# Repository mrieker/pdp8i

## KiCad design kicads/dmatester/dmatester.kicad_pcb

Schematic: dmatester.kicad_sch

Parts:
J1, J2, J3, J4: Conn_02x20_Odd_Even; PinHeader_2x20_P2.54mm_Vertical
J5, J6: Conn_01x24; PinHeader_1x24_P2.54mm_Vertical
U2, U118: 74AC20; DIP-14_W7.62mm
U3: 74HC27; DIP-14_W7.62mm
U4, U5, U10, U12, U13, U18, U19, U24: 74AHC540; DIP-20_W7.62mm
U14: 74AHC02; DIP-14_W7.62mm
U15, U16, U17, U26, U27, U28, U29, U33, U34, U35, U36, U37, U39, U40, U42, U43, U44: 74AHC174; DIP-16_W7.62mm
U20, U124, U125, U141: 74AHC04; DIP-14_W7.62mm
U22, U38, U116, U157, U163: 74HC30; DIP-14_W7.62mm
U41, U169: 74AHC74; DIP-14_W7.62mm
U45: 74AHC86; DIP-14_W7.62mm
U54: 74AHC08; DIP-14_W7.62mm
U147, U158, U161: 74AHC00; DIP-14_W7.62mm
U149: 74AC10; DIP-14_W7.62mm
U155: 74HC21; DIP-14_W7.62mm
U167: 74AC11; DIP-14_W7.62mm
U174: 74AC109; DIP-16_W7.62mm
U180: 74AHC541; DIP-20_W7.62mm

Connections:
/CLOK2: J4.3, U10.7 (A5)
/_ACCLEAR: J3.27
/_ACUM_0: J3.4
/_ACUM_1: J2.33
/_ACUM_2: J2.26
/_ACUM_3: J2.19
/_ACUM_4: J2.12
/_ACUM_5: J2.6
/_ACUM_6: J1.36
/_ACUM_7: J1.30
/_ACUM_8: J1.24
/_ACUM_9: J1.17
/_ACUM_10: J1.10
/_ACUM_11: J1.3
/_BRKCYC: J4.32, U12.7 (A5)
/_BRKGNTI: J4.30, U180.8 (A6)
/_BRKGNTO: J4.29, U180.11 (Y7)
/_BRKRQST: J3.28, U12.12 (Y6), U180.7 (A5)
/_BRKWRM: J4.9, U4.13 (Y5)
/_BUSINI: J3.30, U10.6 (A4)
/_BWCOV: J3.31, U12.9 (A7)
/_CAINC: J4.10, U4.14 (Y4)
/_CYCLE3: J4.11, U4.15 (Y3)
/_DFLD_0: J3.19
/_DFLD_1: J3.15
/_DFLD_2: J3.11
/_DMAFLD_0: J3.20, U4.16 (Y2)
/_DMAFLD_1: J3.16, U4.17 (Y1)
/_DMAFLD_2: J3.12, U4.18 (Y0)
/_FIELD_0: J3.22
/_FIELD_1: J3.18
/_FIELD_2: J3.14
/_IFLD_0: J3.21
/_IFLD_1: J3.17
/_IFLD_2: J3.13
/_INBUS_0: J3.7, U13.18 (Y0), U18.18 (Y0)
/_INBUS_1: J2.36, U13.17 (Y1), U18.17 (Y1)
/_INBUS_2: J2.29, U13.16 (Y2), U18.16 (Y2)
/_INBUS_3: J2.22, U13.15 (Y3), U18.15 (Y3)
/_INBUS_4: J2.15, U13.14 (Y4), U18.14 (Y4)
/_INBUS_5: J2.9, U13.13 (Y5), U18.13 (Y5)
/_INBUS_6: J2.3, U19.18 (Y0), U24.18 (Y0)
/_INBUS_7: J1.33, U19.17 (Y1), U24.17 (Y1)
/_INBUS_8: J1.27, U19.16 (Y2), U24.16 (Y2)
/_INBUS_9: J1.20, U19.15 (Y3), U24.15 (Y3)
/_INBUS_10: J1.13, U19.14 (Y4), U24.14 (Y4)
/_INBUS_11: J1.6, U19.13 (Y5), U24.13 (Y5)
/_INTINH: J4.13
/_INTRQST: J4.14
/_ION: J3.29
/_IOP: J4.6
/_IOSKIP: J4.15
/_IREG_9: J1.23
/_IREG_10: J1.16
/_IREG_11: J1.9
/_LINK: J4.7
/_LNKTOG: J4.16
/_MADR_0: J3.5
/_MADR_1: J2.34
/_MADR_2: J2.27
/_MADR_3: J2.20
/_MADR_4: J2.13
/_MADR_5: J2.7
/_MADR_6: J1.37
/_MADR_7: J1.31
/_MADR_8: J1.25
/_MADR_9: J1.18
/_MADR_10: J1.11
/_MADR_11: J1.4
/_MAJST_0: J4.20
/_MAJST_1: J4.19
/_MAJST_2: J4.18
/_MAJST_3: J4.17
/_MBUF_0: J3.6, U10.5 (A3)
/_MBUF_1: J2.35, U10.4 (A2)
/_MBUF_2: J2.28, U10.3 (A1)
/_MBUF_3: J2.21, U10.2 (A0)
/_MBUF_4: J2.14, U5.9 (A7)
/_MBUF_5: J2.8, U5.8 (A6)
/_MBUF_6: J1.38, U5.7 (A5)
/_MBUF_7: J1.32, U5.6 (A4)
/_MBUF_8: J1.26, U5.5 (A3)
/_MBUF_9: J1.19, U5.4 (A2)
/_MBUF_10: J1.12, U5.3 (A1)
/_MBUF_11: J1.5, U5.2 (A0)
/_MEMDIS: J3.25
/_MQUO_0: J3.8
/_MQUO_1: J2.37
/_MQUO_2: J2.30
/_MQUO_3: J2.23
/_MQUO_4: J2.16
/_MQUO_5: J2.10
/_MQUO_6: J2.4
/_MQUO_7: J1.34
/_MQUO_8: J1.28
/_MQUO_9: J1.21
/_MQUO_10: J1.14
/_MQUO_11: J1.7
/_PAUSE: J4.12
/_PCTR_0: J3.9
/_PCTR_1: J2.38
/_PCTR_2: J2.31
/_PCTR_3: J2.24
/_PCTR_4: J2.17
/_PCTR_5: J2.11
/_PCTR_6: J2.5
/_PCTR_7: J1.35
/_PCTR_8: J1.29
/_PCTR_9: J1.22
/_PCTR_10: J1.15
/_PCTR_11: J1.8
/_READSR: J3.26
/_RESET: J4.4, U10.8 (A6)
/_RUN: J4.8
/_SCTR_0: J3.10
/_SCTR_1: J3.3
/_SCTR_2: J2.32
/_SCTR_3: J2.25
/_SCTR_4: J2.18
/_SWCONT: J3.35
/_SWDEPOS: J3.34
/_SWEXAM: J3.33
/_SWLDAD: J3.32
/_SWSINST: J3.38
/_SWSSTEP: J3.37
/_SWSTART: J3.36
/_TP1: J4.25
/_TP2: J4.26, U12.2 (A0)
/_TP3: J4.27, U12.3 (A1)
/_TP4: J4.28
/_TS1: J4.21
/_TS2: J4.22, U12.4 (A2)
/_TS3: J4.23, U12.5 (A3)
/_TS4: J4.24, U12.6 (A4)
/_brkgnti: U124.13, U167.3, U180.12 (Y6)
/_brkgnto: U158.11, U180.9 (A7)
/_brkrqst: U167.4, U180.13 (Y5)
/_clok1: U10.13 (Y5), U33.9 (Cp), U34.9 (Cp), U35.9 (Cp), U36.9 (Cp), U37.9 (Cp), U39.9 (Cp), U40.9 (Cp), U42.9 (Cp), U43.9 (Cp), U44.9 (Cp)
/_enad: U18.1 (G1), U18.19 (G2), U19.1 (G1), U19.19 (G2), U147.8
/_enwd: U13.1 (G1), U13.19 (G2), U24.1 (G1), U24.19 (G2), U149.8
/_isgranted: U4.1 (G1), U141.10
/addr_0: J6.1, U18.2 (A0), U27.15 (Q5)
/addr_1: J6.2, U18.3 (A1), U27.12 (Q4)
/addr_2: J6.3, U18.4 (A2), U27.10 (Q3)
/addr_3: J6.4, U18.5 (A3), U27.7 (Q2)
/addr_4: J6.5, U18.6 (A4), U27.5 (Q1)
/addr_5: J6.6, U18.7 (A5), U27.2 (Q0)
/addr_6: J6.7, U19.2 (A0), U26.15 (Q5)
/addr_7: J6.8, U19.3 (A1), U26.12 (Q4)
/addr_8: J6.9, U19.4 (A2), U26.10 (Q3)
/addr_9: J6.10, U19.5 (A3), U26.7 (Q2)
/addr_10: J6.11, U19.6 (A4), U26.5 (Q1)
/addr_11: J6.12, U19.7 (A5), U26.2 (Q0)
/addr_12: J6.13, U4.4 (A2), U17.15 (Q5)
/addr_13: J6.14, U4.3 (A1), U17.12 (Q4)
/addr_14: J6.15, U4.2 (A0), U17.10 (Q3)
/blkgntpass: U169.13 (~R), U174.6 (Q)
/brkcyc: U12.13 (Y5), U54.10
/brkgnti: U14.6, U54.5, U124.12, U158.13
/busini: U10.14 (Y4), U14.8, U125.5
/bwcov: U12.11 (Y7), U41.12 (D)
/caincreq: J6.18, U4.6 (A4), U17.5 (Q1)
/cycl3req: J6.17, U4.5 (A3), U17.2 (Q0)
/dorequest: U14.13, U167.5
/endofbrk: U54.1, U54.8, U149.9
/isgranted: U54.6, U54.9, U141.11, U147.9
/lfsr_0: U27.14 (D5), U37.13 (D4), U37.15 (Q5)
/lfsr_1: U27.13 (D4), U37.11 (D3), U37.12 (Q4)
/lfsr_2: U27.11 (D3), U37.6 (D2), U37.10 (Q3)
/lfsr_3: U27.6 (D2), U37.4 (D1), U37.7 (Q2)
/lfsr_4: U27.4 (D1), U37.3 (D0), U37.5 (Q1)
/lfsr_5: U27.3 (D0), U36.14 (D5), U37.2 (Q0)
/lfsr_6: U26.14 (D5), U36.13 (D4), U36.15 (Q5)
/lfsr_7: U26.13 (D4), U36.11 (D3), U36.12 (Q4)
/lfsr_8: U26.11 (D3), U36.6 (D2), U36.10 (Q3)
/lfsr_9: U26.6 (D2), U36.4 (D1), U36.7 (Q2)
/lfsr_10: U26.4 (D1), U36.3 (D0), U36.5 (Q1)
/lfsr_11: U26.3 (D0), U35.14 (D5), U36.2 (Q0)
/lfsr_12: U17.14 (D5), U35.15 (Q5), U45.5
/lfsr_13: U17.13 (D4), U35.11 (D3), U35.12 (Q4)
/lfsr_14: U17.11 (D3), U35.6 (D2), U35.10 (Q3)
/lfsr_15: U17.6 (D2), U35.4 (D1), U35.7 (Q2)
/lfsr_16: U17.4 (D1), U35.3 (D0), U35.5 (Q1)
/lfsr_17: U17.3 (D0), U34.14 (D5), U35.2 (Q0)
/lfsr_18: U16.14 (D5), U34.15 (Q5), U45.10
/lfsr_19: U16.13 (D4), U34.11 (D3), U34.12 (Q4)
/lfsr_20: U16.11 (D3), U34.6 (D2), U34.10 (Q3)
/lfsr_21: U16.6 (D2), U34.4 (D1), U34.7 (Q2)
/lfsr_22: U16.4 (D1), U34.3 (D0), U34.5 (Q1)
/lfsr_23: U16.3 (D0), U33.14 (D5), U34.2 (Q0)
/lfsr_24: U15.14 (D5), U33.15 (Q5), U45.13
/lfsr_25: U15.13 (D4), U33.11 (D3), U33.12 (Q4)
/lfsr_26: U15.11 (D3), U33.6 (D2), U33.10 (Q3)
/lfsr_27: U15.6 (D2), U33.4 (D1), U33.7 (Q2)
/lfsr_28: U15.4 (D1), U33.3 (D0), U33.5 (Q1)
/lfsr_29: U15.3 (D0), U33.2 (Q0), U44.14 (D5)
/lfsr_30: U44.13 (D4), U44.15 (Q5)
/lfsr_31: U44.11 (D3), U44.12 (Q4)
/lfsr_32: U44.6 (D2), U44.10 (Q3)
/lfsr_33: U44.4 (D1), U44.7 (Q2)
/lfsr_34: U44.3 (D0), U44.5 (Q1)
/lfsr_35: U43.14 (D5), U44.2 (Q0)
/lfsr_36: U43.13 (D4), U43.15 (Q5)
/lfsr_37: U43.11 (D3), U43.12 (Q4)
/lfsr_38: U43.6 (D2), U43.10 (Q3)
/lfsr_39: U43.4 (D1), U43.7 (Q2)
/lfsr_40: U43.3 (D0), U43.5 (Q1)
/lfsr_41: U42.14 (D5), U43.2 (Q0)
/lfsr_42: U42.13 (D4), U42.15 (Q5)
/lfsr_43: U42.11 (D3), U42.12 (Q4)
/lfsr_44: U42.6 (D2), U42.10 (Q3)
/lfsr_45: U42.4 (D1), U42.7 (Q2)
/lfsr_46: U42.3 (D0), U42.5 (Q1)
/lfsr_47: U40.14 (D5), U42.2 (Q0)
/lfsr_48: U40.13 (D4), U40.15 (Q5)
/lfsr_49: U40.11 (D3), U40.12 (Q4), U147.5
/lfsr_50: U40.6 (D2), U40.10 (Q3)
/lfsr_51: U40.4 (D1), U40.7 (Q2), U147.4
/lfsr_52: U38.12, U40.3 (D0), U40.5 (Q1)
/lfsr_53: U38.11, U39.14 (D5), U40.2 (Q0)
/lfsr_54: U38.6, U39.13 (D4), U39.15 (Q5)
/lfsr_55: U38.5, U39.11 (D3), U39.12 (Q4)
/lfsr_56: U38.4, U39.6 (D2), U39.10 (Q3)
/lfsr_57: U38.3, U39.4 (D1), U39.7 (Q2)
/lfsr_58: U38.2, U39.3 (D0), U39.5 (Q1), U45.2
/lfsr_59: U38.1, U39.2 (Q0), U45.1
/mbuf_0: U10.15 (Y3), U29.14 (D5)
/mbuf_1: U10.16 (Y2), U29.13 (D4)
/mbuf_2: U10.17 (Y1), U29.11 (D3)
/mbuf_3: U10.18 (Y0), U29.6 (D2)
/mbuf_4: U5.11 (Y7), U29.4 (D1)
/mbuf_5: U5.12 (Y6), U29.3 (D0)
/mbuf_6: U5.13 (Y5), U28.14 (D5)
/mbuf_7: U5.14 (Y4), U28.13 (D4)
/mbuf_8: U5.15 (Y3), U28.11 (D3)
/mbuf_9: U5.16 (Y2), U28.6 (D2)
/mbuf_10: U5.17 (Y1), U28.4 (D1)
/mbuf_11: U5.18 (Y0), U28.3 (D0)
/rdata_0: J5.13, U29.15 (Q5)
/rdata_1: J5.14, U29.12 (Q4)
/rdata_2: J5.15, U29.10 (Q3)
/rdata_3: J5.16, U29.7 (Q2)
/rdata_4: J5.17, U29.5 (Q1)
/rdata_5: J5.18, U29.2 (Q0)
/rdata_6: J5.19, U28.15 (Q5)
/rdata_7: J5.20, U28.12 (Q4)
/rdata_8: J5.21, U28.10 (Q3)
/rdata_9: J5.22, U28.7 (Q2)
/rdata_10: J5.23, U28.5 (Q1)
/rdata_11: J5.24, U28.2 (Q0)
/reset: U10.12 (Y6)
/rqstout: U12.8 (A6), U14.5, U15.9 (Cp), U16.9 (Cp), U17.9 (Cp), U26.9 (Cp), U27.9 (Cp), U54.4, U174.10 (Q)
/seed_0: J6.24, U45.4
/seed_1: J6.23, U45.9
/seed_2: J6.22, U45.12
/tp2: U12.18 (Y0), U54.2
/tp3: U12.17 (Y1)
/ts2: U12.16 (Y2), U149.11
/ts3: U12.15 (Y3)
/ts4: U12.14 (Y4), U147.10
/wcover: J6.16, U41.9 (Q)
/wdata_0: J5.1, U13.2 (A0), U16.15 (Q5)
/wdata_1: J5.2, U13.3 (A1), U16.12 (Q4)
/wdata_2: J5.3, U13.4 (A2), U16.10 (Q3)
/wdata_3: J5.4, U13.5 (A3), U16.7 (Q2)
/wdata_4: J5.5, U13.6 (A4), U16.5 (Q1)
/wdata_5: J5.6, U13.7 (A5), U16.2 (Q0)
/wdata_6: J5.7, U15.15 (Q5), U24.2 (A0)
/wdata_7: J5.8, U15.12 (Q4), U24.3 (A1)
/wdata_8: J5.9, U15.10 (Q3), U24.4 (A2)
/wdata_9: J5.10, U15.7 (Q2), U24.5 (A3)
/wdata_10: J5.11, U15.5 (Q1), U24.6 (A4)
/wdata_11: J5.12, U15.2 (Q0), U24.7 (A5)
/wrmemreq: J6.19, U4.7 (A5), U17.7 (Q2), U149.10
GND: J1.39, J1.40, J2.39, J2.40, J3.39, J3.40, J4.39, J4.40, U2.1, U2.2, U2.4, U2.5, U2.7 (GND), U3.3, U3.4, U3.5, U3.7 (GND), U4.8 (A6), U4.9 (A7), U4.10 (GND), U4.19 (G2), U5.1 (G1), U5.10 (GND), U5.19 (G2), U10.1 (G1), U10.9 (A7), U10.10 (GND), U10.19 (G2), U12.1 (G1), U12.10 (GND), U12.19 (G2), U13.8 (A6), U13.9 (A7), U13.10 (GND), U14.7 (GND), U15.8 (GND), U16.8 (GND), U17.8 (GND), U18.8 (A6), U18.9 (A7), U18.10 (GND), U19.8 (A6), U19.9 (A7), U19.10 (GND), U20.3, U20.7 (GND), U22.7 (GND), U24.8 (A6), U24.9 (A7), U24.10 (GND), U26.8 (GND), U27.8 (GND), U28.8 (GND), U29.8 (GND), U33.8 (GND), U34.8 (GND), U35.8 (GND), U36.8 (GND), U37.8 (GND), U38.7 (GND), U39.8 (GND), U40.8 (GND), U41.7 (GND), U42.8 (GND), U43.8 (GND), U44.8 (GND), U45.7 (GND), U54.7 (GND), U54.12, U54.13, U116.7 (GND), U118.1, U118.2, U118.4, U118.5, U118.7 (GND), U118.9, U118.10, U118.12, U118.13, U124.5, U124.7 (GND), U125.7 (GND), U141.7 (GND), U147.7 (GND), U149.7 (GND), U155.1, U155.2, U155.4, U155.5, U155.7 (GND), U155.9, U155.10, U155.12, U155.13, U157.7 (GND), U158.7 (GND), U161.7 (GND), U163.7 (GND), U167.1, U167.2, U167.7 (GND), U167.13, U169.7 (GND), U174.8 (GND), U180.1 (G1), U180.10 (GND), U180.19 (G2)
unnamed: U14.11, U38.8
unnamed: U14.12, U147.6
unnamed: U20.13, U45.3
unnamed: U14.9, U28.9 (Cp), U29.9 (Cp), U41.11 (C), U54.3
unnamed: U33.13 (D4), U45.11
unnamed: U34.13 (D4), U45.8
unnamed: U35.13 (D4), U45.6
unnamed: U20.12, U37.14 (D5)
unnamed: U14.4, U169.11 (C)
unnamed: U169.8 (~Q), U174.1 (~R)
unnamed: U125.6, U169.10 (~S)
unnamed: U167.6, U174.4 (C), U174.12 (C)
unnamed: U158.12, U174.7 (~Q)
unnamed: U14.10, U174.15 (~R)
VCC: J1.1, J1.2, J2.1, J2.2, J3.1, J3.2, J4.1, J4.2, U2.14 (VCC), U3.14 (VCC), U4.20 (VCC), U5.20 (VCC), U10.20 (VCC), U12.20 (VCC), U13.20 (VCC), U14.14 (VCC), U15.1 (~Mr), U15.16 (VCC), U16.1 (~Mr), U16.16 (VCC), U17.1 (~Mr), U17.16 (VCC), U18.20 (VCC), U19.20 (VCC), U20.14 (VCC), U22.14 (VCC), U24.20 (VCC), U26.1 (~Mr), U26.16 (VCC), U27.1 (~Mr), U27.16 (VCC), U28.1 (~Mr), U28.16 (VCC), U29.1 (~Mr), U29.16 (VCC), U33.1 (~Mr), U33.16 (VCC), U34.1 (~Mr), U34.16 (VCC), U35.1 (~Mr), U35.16 (VCC), U36.1 (~Mr), U36.16 (VCC), U37.1 (~Mr), U37.16 (VCC), U38.14 (VCC), U39.1 (~Mr), U39.16 (VCC), U40.1 (~Mr), U40.16 (VCC), U41.10 (~S), U41.13 (~R), U41.14 (VCC), U42.1 (~Mr), U42.16 (VCC), U43.1 (~Mr), U43.16 (VCC), U44.1 (~Mr), U44.16 (VCC), U45.14 (VCC), U54.14 (VCC), U116.14 (VCC), U118.14 (VCC), U124.14 (VCC), U125.14 (VCC), U141.14 (VCC), U147.14 (VCC), U149.14 (VCC), U155.14 (VCC), U157.14 (VCC), U158.14 (VCC), U161.14 (VCC), U163.14 (VCC), U167.14 (VCC), U169.12 (D), U169.14 (VCC), U174.2 (J), U174.3 (~K), U174.5 (~S), U174.11 (~S), U174.13 (~K), U174.14 (J), U174.16 (VCC), U180.20 (VCC)

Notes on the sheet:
resume passing grant along when * we have dropped our request and * we are no longer receiving grant from next inner dma
end of our break cycle = our break request has been granted and processor is doing a break cycle
our break request has been granted
stop requesting break when getting TP2 pulse of a BREAK cycle that we have been granted
start requesting break when * no break is being granted * no break is being requested * this circuit wants to do a break also start blocking outgoing break grant
pass brkgnti on to brkgnto unless we are requesting a break we don't start requesting a break when a grant is already in progress

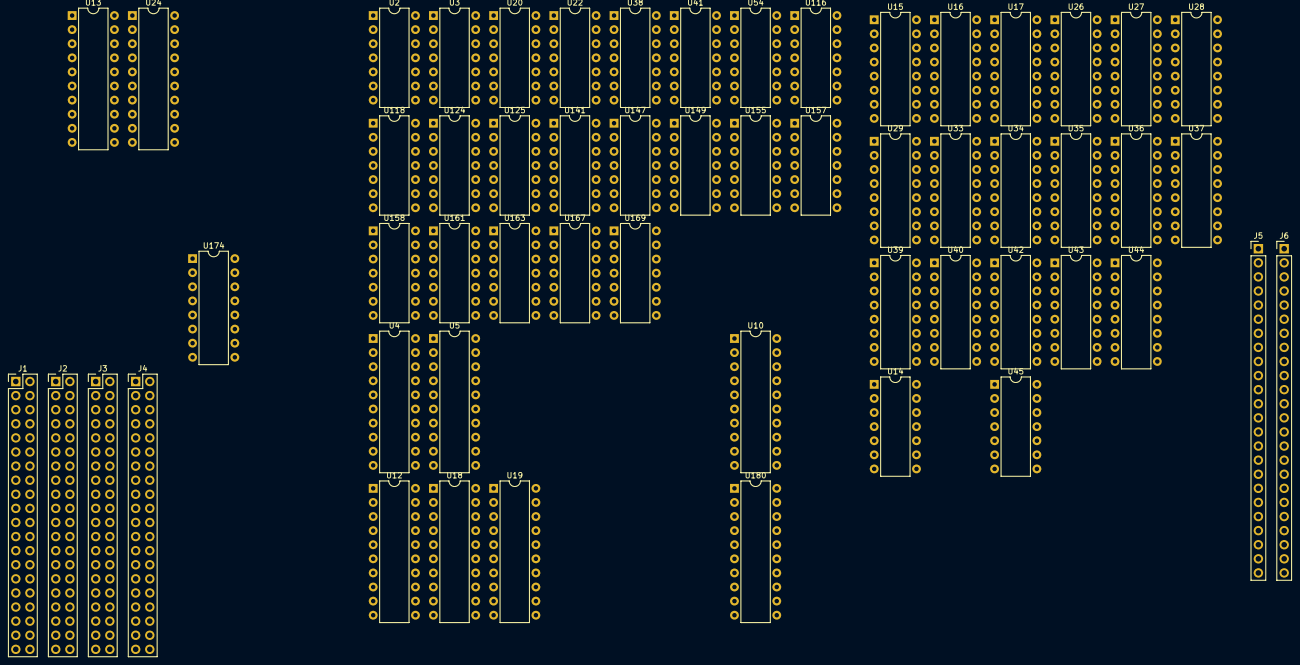
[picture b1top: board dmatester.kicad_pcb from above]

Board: 2 copper layers, 56 parts (0 on the bottom side), 196 nets, no tracks yet.

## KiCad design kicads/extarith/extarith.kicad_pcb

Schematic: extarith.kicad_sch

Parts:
J1, J2, J3, J4: Conn_01x36; PinHeader_1x36_P2.54mm_Vertical
U1, U145, U152, U154: 74HC27; DIP-14_W7.62mm
U2, U167: 74AC11; DIP-14_W7.62mm
U3, U8, U124, U125, U141: 74AHC04; DIP-14_W7.62mm
U4, U5: 74AC161; DIP-16_W7.62mm
U6, U157, U162: 74HC30; DIP-14_W7.62mm
U9, U10, U11, U12, U13, U14, U15, U16, U17, U22, U23: 74AHC540; DIP-20_W7.62mm
U24, U139: 74AC175; DIP-16_W7.62mm
U25, U30: 74AHC157; DIP-16_W7.62mm
U41, U90: 74AHC74; DIP-14_W7.62mm
U44, U82, U91, U107, U108, U109, U113, U120, U127, U147, U151, U158, U161, U168: 74AHC00; DIP-14_W7.62mm
U51, U142, U144: 74AHC02; DIP-14_W7.62mm
U54: 74AHC08; DIP-14_W7.62mm
U75, U78, U81, U187, U188, U189: 74AC283; DIP-16_W7.62mm
U89: 74AHC86; DIP-14_W7.62mm
U92, U93, U94, U95, U96, U97, U98, U99, U100, U101, U102, U103, U104, U175, U176, U177, U178, U179, U180, U181, U182, U183, U184, U185, U186: 74AC151; DIP-16_W7.62mm
U110: 74AHC32; DIP-14_W7.62mm
U122: 74AC20; DIP-14_W7.62mm
U129, U130, U131, U132: 74AHC174; DIP-16_W7.62mm
U143, U146, U148, U149, U150, U160: 74AC10; DIP-14_W7.62mm
U192, U193, U194: 74HC85; DIP-16_W7.62mm

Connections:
/CONSCK: J4.35
/CONSDA: J4.34
/_ACCLEAR: J3.28, U22.14 (Y4)
/_ACUM_0: J3.7, U12.2 (A0)
/_ACUM_1: J2.34, U16.5 (A3)
/_ACUM_2: J2.27, U11.8 (A6)
/_ACUM_3: J2.20, U11.3 (A1)
/_ACUM_4: J2.13, U15.6 (A4)
/_ACUM_5: J2.7, U15.2 (A0)
/_ACUM_6: J1.35, U10.6 (A4)
/_ACUM_7: J1.29, U10.2 (A0)
/_ACUM_8: J1.23, U14.6 (A4)
/_ACUM_9: J1.16, U14.2 (A0)
/_ACUM_10: J1.9, U9.6 (A4)
/_ACUM_11: J1.2, U9.2 (A0)
/_BRKCYC: J4.33
/_BRKGNTI: J4.32
/_BRKGNTO: J4.31
/_BRKRQST: J3.29
/_BRKWRM: J4.11
/_BUSINI: J3.31, U12.7 (A5)
/_BWCOV: J3.32
/_CAINC: J4.12
/_CLOCK: J4.6, U12.8 (A6)
/_CYCLE3: J4.13
/_DFLD_0: J3.22
/_DFLD_1: J3.18
/_DFLD_2: J3.14
/_DMAFLD_0: J3.23
/_DMAFLD_1: J3.19
/_DMAFLD_2: J3.15
/_IFLD_0: J3.24
/_IFLD_1: J3.20
/_IFLD_2: J3.16
/_INBUS_0: J3.10, U12.4 (A2), U23.18 (Y0)
/_INBUS_1: J3.3, U16.7 (A5), U23.17 (Y1)
/_INBUS_2: J2.30, U16.2 (A0), U23.16 (Y2)
/_INBUS_3: J2.23, U11.5 (A3), U23.15 (Y3)
/_INBUS_4: J2.16, U15.8 (A6), U23.14 (Y4)
/_INBUS_5: J2.10, U15.4 (A2), U23.13 (Y5)
/_INBUS_6: J2.4, U10.8 (A6), U23.12 (Y6)
/_INBUS_7: J1.32, U10.4 (A2), U23.11 (Y7)
/_INBUS_8: J1.26, U14.8 (A6), U22.18 (Y0)
/_INBUS_9: J1.19, U14.4 (A2), U22.17 (Y1)
/_INBUS_10: J1.12, U9.8 (A6), U22.16 (Y2)
/_INBUS_11: J1.5, U9.4 (A2), U22.15 (Y3)
/_INTINH: J4.15
/_INTRQST: J4.16
/_ION: J3.30
/_IOP: J4.8
/_IOSKIP: J4.17, U22.13 (Y5)
/_IREG_9: J1.22
/_IREG_10: J1.15
/_IREG_11: J1.8
/_LINK: J4.9, U12.9 (A7)
/_LNKTOG: J4.18, U22.12 (Y6)
/_MADR_0: J3.8
/_MADR_1: J2.35
/_MADR_2: J2.28
/_MADR_3: J2.21
/_MADR_4: J2.14
/_MADR_5: J2.8
/_MADR_6: J2.2
/_MADR_7: J1.30
/_MADR_8: J1.24
/_MADR_9: J1.17
/_MADR_10: J1.10
/_MADR_11: J1.3
/_MAJST_0: J4.22, U17.6 (A4)
/_MAJST_1: J4.21, U17.5 (A3)
/_MAJST_2: J4.20, U17.4 (A2)
/_MAJST_3: J4.19, U17.3 (A1)
/_MBUF_0: J3.9, U12.3 (A1)
/_MBUF_1: J3.2, U16.6 (A4)
/_MBUF_2: J2.29, U11.9 (A7)
/_MBUF_3: J2.22, U11.4 (A2)
/_MBUF_4: J2.15, U15.7 (A5)
/_MBUF_5: J2.9, U15.3 (A1)
/_MBUF_6: J2.3, U10.7 (A5)
/_MBUF_7: J1.31, U10.3 (A1)
/_MBUF_8: J1.25, U14.7 (A5)
/_MBUF_9: J1.18, U14.3 (A1)
/_MBUF_10: J1.11, U9.7 (A5)
/_MBUF_11: J1.4, U9.3 (A1)
/_MEAD_0: J3.25
/_MEAD_1: J3.21
/_MEAD_2: J3.17
/_MEMDIS: J3.26
/_MQUO_0: J3.11, U12.15 (Y3)
/_MQUO_1: J3.4, U16.12 (Y6)
/_MQUO_2: J2.31, U16.17 (Y1)
/_MQUO_3: J2.24, U11.14 (Y4)
/_MQUO_4: J2.17, U15.11 (Y7)
/_MQUO_5: J2.11, U15.15 (Y3)
/_MQUO_6: J2.5, U10.11 (Y7)
/_MQUO_7: J1.33, U10.15 (Y3)
/_MQUO_8: J1.27, U14.11 (Y7)
/_MQUO_9: J1.20, U14.15 (Y3)
/_MQUO_10: J1.13, U9.11 (Y7)
/_MQUO_11: J1.6, U9.15 (Y3)
/_PAUSE: J4.14, U17.18 (Y0)
/_PCTR_0: J3.12
/_PCTR_1: J3.5
/_PCTR_2: J2.32
/_PCTR_3: J2.25
/_PCTR_4: J2.18
/_PCTR_5: J2.12
/_PCTR_6: J2.6
/_PCTR_7: J1.34
/_PCTR_8: J1.28
/_PCTR_9: J1.21
/_PCTR_10: J1.14
/_PCTR_11: J1.7
/_READSR: J3.27
/_RESET: J4.7
/_RUN: J4.10
/_SCTR_0: J3.13, U12.14 (Y4)
/_SCTR_1: J3.6, U16.11 (Y7)
/_SCTR_2: J2.33, U16.16 (Y2)
/_SCTR_3: J2.26, U11.13 (Y5)
/_SCTR_4: J2.19, U11.18 (Y0)
/_SWCONT: J4.2
/_SWDEPOS: J3.35
/_SWEXAM: J3.34
/_SWLDAD: J3.33
/_SWSINST: J4.5
/_SWSSTEP: J4.4
/_SWSTART: J4.3
/_TP1: J4.27, U13.2 (A0)
/_TP2: J4.28, U13.3 (A1)
/_TP3: J4.29
/_TP4: J4.30
/_TS1: J4.23, U17.7 (A5)
/_TS2: J4.24, U17.8 (A6)
/_TS3: J4.25, U17.9 (A7)
/_TS4: J4.26
/_busini: U3.12, U4.1 (~MR), U5.1 (~MR), U24.1 (~Mr), U131.1 (~Mr), U132.1 (~Mr), U139.1 (~Mr)
/_dviover: U90.5 (Q), U150.11
/_enouts: U22.1 (G1), U22.19 (G2), U23.1 (G1), U23.19 (G2), U168.11
/_ensctrld: U4.9 (~PE), U5.9 (~PE), U146.6
/_extar: U139.11 (~Q2)
/_extarex: U141.11, U157.8
/_extop_1: U24.3 (~Q0), U127.4, U146.13, U148.1, U167.3, U167.11
/_extop_2: U24.6 (~Q1), U127.5, U146.2, U167.4, U167.10
/_extop_3: U24.11 (~Q2), U90.13 (~R), U144.9, U146.1, U148.5, U148.13, U158.9
/_extop_4: U24.14 (~Q3), U44.1, U44.9, U91.4, U108.1, U108.12, U109.1, U109.12, U113.9, U120.4, U120.12, U151.1, U151.12
/_extop_5: U139.3 (~Q0)
/_extop_6: U139.6 (~Q1)
/_extop_dvi: U141.9, U142.9, U148.6
/_extop_muy: U141.5, U142.12, U148.12
/_majst_1: U8.8, U82.2
/_majst_2: U8.10, U157.6
/_majst_3: U8.12, U157.11
/_nmidone: U54.6, U147.5
/_s3clk: U41.5 (Q), U127.13, U143.10, U149.13, U158.13, U168.10
/_ts2: U141.2, U149.5, U149.11
/_ts3: U51.3, U51.12, U141.4, U145.5, U145.13, U158.2
/_yreg_0: U30.3 (I1a), U125.2, U187.6 (B1)
/_yreg_1: U30.6 (I1b), U125.4, U187.2 (B2)
/_yreg_2: U30.10 (I1c), U125.6, U187.15 (B3)
/_yreg_3: U30.13 (I1d), U125.8, U187.11 (B4)
/_yreg_4: U25.3 (I1a), U125.10, U188.6 (B1)
/_yreg_5: U125.12, U188.2 (B2)
/_yreg_6: U124.2, U188.15 (B3)
/_yreg_7: U124.4, U188.11 (B4)
/_yreg_8: U124.6, U189.6 (B1)
/_yreg_9: U124.8, U189.2 (B2)
/_yreg_10: U124.10, U189.15 (B3)
/_yreg_11: U124.12, U189.11 (B4)
/acclk: U41.11 (C), U129.9 (Cp), U130.9 (Cp), U149.12
/acmux_0: U129.3 (D0), U186.5 (Z)
/acmux_1: U129.4 (D1), U185.5 (Z)
/acmux_2: U129.6 (D2), U184.5 (Z)
/acmux_3: U129.11 (D3), U183.5 (Z)
/acmux_4: U129.13 (D4), U182.5 (Z)
/acmux_5: U129.14 (D5), U181.5 (Z)
/acmux_6: U130.3 (D0), U180.5 (Z)
/acmux_7: U130.4 (D1), U179.5 (Z)
/acmux_8: U130.6 (D2), U178.5 (Z)
/acmux_9: U130.11 (D3), U177.5 (Z)
/acmux_10: U130.13 (D4), U176.5 (Z)
/acmux_11: U130.14 (D5), U175.5 (Z)
/acsel_0: U149.8, U175.11 (S0), U176.11 (S0), U177.11 (S0), U178.11 (S0), U179.11 (S0), U180.11 (S0), U181.11 (S0), U182.11 (S0), U183.11 (S0), U184.11 (S0), U185.11 (S0), U186.11 (S0)
/acsel_1: U145.6, U175.10 (S1), U176.10 (S1), U177.10 (S1), U178.10 (S1), U179.10 (S1), U180.10 (S1), U181.10 (S1), U182.10 (S1), U183.10 (S1), U184.10 (S1), U185.10 (S1), U186.10 (S1)
/acsel_2: U51.13, U175.9 (S2), U176.9 (S2), U177.9 (S2), U178.9 (S2), U179.9 (S2), U180.9 (S2), U181.9 (S2), U182.9 (S2), U183.9 (S2), U184.9 (S2), U185.9 (S2), U186.9 (S2)
/acsel_zero: U54.11, U175.7 (~E), U176.7 (~E), U177.7 (~E), U178.7 (~E), U179.7 (~E), U180.7 (~E), U181.7 (~E), U182.7 (~E), U183.7 (~E), U184.7 (~E), U185.7 (~E), U186.7 (~E)
/acum_0: U12.18 (Y0), U186.4 (I0)
/acum_1: U16.15 (Y3), U185.4 (I0)
/acum_2: U11.12 (Y6), U184.4 (I0)
/acum_3: U11.17 (Y1), U183.4 (I0)
/acum_4: U15.14 (Y4), U182.4 (I0)
/acum_5: U15.18 (Y0), U181.4 (I0)
/acum_6: U10.14 (Y4), U180.4 (I0)
/acum_7: U10.18 (Y0), U179.4 (I0)
/acum_8: U14.14 (Y4), U178.4 (I0)
/acum_9: U14.18 (Y0), U177.4 (I0)
/acum_10: U9.14 (Y4), U176.4 (I0)
/acum_11: U9.18 (Y0), U175.4 (I0)
/busini: U3.13, U12.13 (Y5)
/clock: U12.12 (Y6), U41.3 (C), U90.11 (C)
/clocksctr: U4.2 (CP), U5.2 (CP), U168.8
/countedshift: U144.10, U147.9
/dvi_shl: U142.10, U145.1, U145.3, U145.9
/dviacstep_0: U186.1 (I3), U187.4 (S1)
/dviacstep_1: U185.1 (I3), U187.1 (S2)
/dviacstep_2: U184.1 (I3), U187.13 (S3)
/dviacstep_3: U183.1 (I3), U187.10 (S4)
/dviacstep_4: U182.1 (I3), U188.4 (S1)
/dviacstep_5: U181.1 (I3), U188.1 (S2)
/dviacstep_6: U180.1 (I3), U188.13 (S3)
/dviacstep_7: U179.1 (I3), U188.10 (S4)
/dviacstep_8: U178.1 (I3), U189.4 (S1)
/dviacstep_9: U177.1 (I3), U189.1 (S2)
/dviacstep_10: U176.1 (I3), U189.13 (S3)
/dviacstep_11: U175.1 (I3), U189.10 (S4)
/dvicarry: U110.13, U189.9 (C4)
/dviover: U90.6 (~Q), U99.1 (I3)
/dviqbit: U96.1 (I3), U110.11, U142.8
/extar: U139.10 (Q2), U157.12
/extarex: U141.10, U146.4, U146.10, U161.5, U167.1, U168.13
/extop_1: U24.2 (Q0), U99.11 (S0), U144.5, U148.3, U161.10
/extop_2: U24.7 (Q1), U51.9, U99.10 (S1), U144.6, U148.2, U148.4, U158.10
/extop_3: U24.10 (Q2), U99.9 (S2), U145.11, U167.5, U167.9
/extop_4: U24.15 (Q3), U146.11
/extop_5: U91.9, U109.4, U113.12, U127.1, U139.2 (Q0), U151.4
/extop_6: U44.4, U44.12, U91.1, U91.12, U108.4, U108.9, U109.9, U113.1, U113.4, U120.1, U120.9, U139.7 (Q1), U151.9
/extop_dvi: U141.8, U150.9
/extop_muy: U141.6, U147.1
/extop_nmi: U147.4, U167.6
/inbus_0: U12.16 (Y2), U127.10
/inbus_1: U16.13 (Y5), U24.4 (D0)
/inbus_2: U16.18 (Y0), U24.5 (D1)
/inbus_3: U11.15 (Y3), U24.12 (D2)
/inbus_4: U15.12 (Y6), U24.13 (D3)
/inbus_5: U15.16 (Y2), U139.4 (D0)
/inbus_6: U10.12 (Y6), U139.5 (D1)
/inbus_7: U10.16 (Y2), U54.13
/inbus_8: U14.12 (Y6), U127.9
/inbus_9: U14.16 (Y2), U150.5
/inbus_10: U9.12 (Y6), U150.4
/inbus_11: U9.16 (Y2), U150.3
/link: U12.11 (Y7), U99.3 (I1), U99.4 (I0), U158.1
/majst_0: U2.10, U17.14 (Y4), U143.4, U157.5
/majst_000x: U1.8, U2.11, U143.5
/majst_1: U1.9, U8.9, U17.15 (Y3)
/majst_2: U1.10, U8.11, U17.16 (Y2)
/majst_3: U1.11, U8.13, U17.17 (Y1)
/memop: U82.1, U127.6
/mqclk: U131.9 (Cp), U132.9 (Cp), U158.11
/mqmux_0: U96.5 (Z), U131.3 (D0)
/mqmux_1: U95.5 (Z), U131.4 (D1)
/mqmux_2: U94.5 (Z), U131.6 (D2)
/mqmux_3: U102.5 (Z), U131.11 (D3)
/mqmux_4: U101.5 (Z), U131.13 (D4)
/mqmux_5: U100.5 (Z), U131.14 (D5)
/mqmux_6: U92.5 (Z), U132.3 (D0)
/mqmux_7: U98.5 (Z), U132.4 (D1)
/mqmux_8: U97.5 (Z), U132.6 (D2)
/mqmux_9: U93.5 (Z), U132.11 (D3)
/mqmux_10: U104.5 (Z), U132.13 (D4)
/mqmux_11: U103.5 (Z), U132.14 (D5)
/mqsel_0: U92.11 (S0), U93.11 (S0), U94.11 (S0), U95.11 (S0), U96.11 (S0), U97.11 (S0), U98.11 (S0), U100.11 (S0), U101.11 (S0), U102.11 (S0), U103.11 (S0), U104.11 (S0), U149.6
/mqsel_1: U92.10 (S1), U93.10 (S1), U94.10 (S1), U95.10 (S1), U96.10 (S1), U97.10 (S1), U98.10 (S1), U100.10 (S1), U101.10 (S1), U102.10 (S1), U103.10 (S1), U104.10 (S1), U145.12
/mqsel_2: U51.1, U92.9 (S2), U93.9 (S2), U94.9 (S2), U95.9 (S2), U96.9 (S2), U97.9 (S2), U98.9 (S2), U100.9 (S2), U101.9 (S2), U102.9 (S2), U103.9 (S2), U104.9 (S2)
/mquo_0: U12.5 (A3), U95.1 (I3), U95.14 (I5), U95.15 (I4), U131.2 (Q0), U142.11, U151.10, U154.1
/mquo_1: U16.8 (A6), U94.1 (I3), U94.14 (I5), U94.15 (I4), U96.2 (I2), U96.12 (I7), U96.13 (I6), U113.5, U131.5 (Q1), U154.2
/mquo_2: U16.3 (A1), U91.2, U95.2 (I2), U95.12 (I7), U95.13 (I6), U102.1 (I3), U102.14 (I5), U102.15 (I4), U131.7 (Q2), U154.13
/mquo_3: U11.6 (A4), U91.13, U94.2 (I2), U94.12 (I7), U94.13 (I6), U101.1 (I3), U101.14 (I5), U101.15 (I4), U131.10 (Q3), U154.3
/mquo_4: U15.9 (A7), U100.1 (I3), U100.14 (I5), U100.15 (I4), U102.2 (I2), U102.12 (I7), U102.13 (I6), U109.10, U131.12 (Q4), U154.4
/mquo_5: U15.5 (A3), U92.1 (I3), U92.14 (I5), U92.15 (I4), U101.2 (I2), U101.12 (I7), U101.13 (I6), U108.10, U131.15 (Q5), U154.5
/mquo_6: U10.9 (A7), U98.1 (I3), U98.14 (I5), U98.15 (I4), U100.2 (I2), U100.12 (I7), U100.13 (I6), U120.2, U132.2 (Q0), U154.9
/mquo_7: U10.5 (A3), U92.2 (I2), U92.12 (I7), U92.13 (I6), U97.1 (I3), U97.14 (I5), U97.15 (I4), U120.10, U132.5 (Q1), U154.10
/mquo_8: U14.9 (A7), U93.1 (I3), U93.14 (I5), U93.15 (I4), U98.2 (I2), U98.12 (I7), U98.13 (I6), U113.2, U132.7 (Q2), U154.11
/mquo_9: U14.5 (A3), U44.5, U97.2 (I2), U97.12 (I7), U97.13 (I6), U104.1 (I3), U104.14 (I5), U104.15 (I4), U132.10 (Q3), U152.1
/mquo_10: U9.9 (A7), U44.13, U93.2 (I2), U93.12 (I7), U93.13 (I6), U103.1 (I3), U103.14 (I5), U103.15 (I4), U132.12 (Q4), U152.2
/mquo_11: U9.5 (A3), U104.2 (I2), U104.12 (I7), U104.13 (I6), U108.5, U132.15 (Q5), U152.13, U186.14 (I5), U186.15 (I4), U187.5 (A1)
/muy_lsr: U51.8, U142.13, U145.10, U161.12
/muyacstep_0: U75.1 (S2), U186.2 (I2)
/muyacstep_1: U75.13 (S3), U185.2 (I2)
/muyacstep_2: U75.10 (S4), U184.2 (I2)
/muyacstep_3: U78.4 (S1), U183.2 (I2)
/muyacstep_4: U78.1 (S2), U182.2 (I2)
/muyacstep_5: U78.13 (S3), U181.2 (I2)
/muyacstep_6: U78.10 (S4), U180.2 (I2)
/muyacstep_7: U81.4 (S1), U179.2 (I2)
/muyacstep_8: U81.1 (S2), U178.2 (I2)
/muyacstep_9: U81.13 (S3), U177.2 (I2)
/muyacstep_10: U81.10 (S4), U176.2 (I2)
/muyacstep_11: U81.9 (C4), U175.2 (I2)
/muymqstep_11: U75.4 (S1), U103.2 (I2)
/myac_0: U23.2 (A0), U75.5 (A1), U96.3 (I1), U103.12 (I7), U103.13 (I6), U129.2 (Q0), U151.2, U152.3, U185.14 (I5), U185.15 (I4), U187.3 (A2), U192.10 (A0)
/myac_1: U23.3 (A1), U75.3 (A2), U95.3 (I1), U129.5 (Q1), U151.13, U152.4, U184.14 (I5), U184.15 (I4), U186.12 (I7), U186.13 (I6), U187.14 (A3), U192.12 (A1)
/myac_2: U23.4 (A2), U75.14 (A3), U94.3 (I1), U113.10, U129.7 (Q2), U152.5, U183.14 (I5), U183.15 (I4), U185.12 (I7), U185.13 (I6), U187.12 (A4), U192.13 (A2)
/myac_3: U23.5 (A3), U75.12 (A4), U91.5, U102.3 (I1), U129.10 (Q3), U152.9, U182.14 (I5), U182.15 (I4), U184.12 (I7), U184.13 (I6), U188.5 (A1), U192.15 (A3)
/myac_4: U23.6 (A4), U78.5 (A1), U101.3 (I1), U109.2, U129.12 (Q4), U152.10, U181.14 (I5), U181.15 (I4), U183.12 (I7), U183.13 (I6), U188.3 (A2), U193.10 (A0)
/myac_5: U23.7 (A5), U78.3 (A2), U100.3 (I1), U109.13, U129.15 (Q5), U152.11, U180.14 (I5), U180.15 (I4), U182.12 (I7), U182.13 (I6), U188.14 (A3), U193.12 (A1)
/myac_6: U23.8 (A6), U78.14 (A3), U92.3 (I1), U108.13, U130.2 (Q0), U144.2, U179.14 (I5), U179.15 (I4), U181.12 (I7), U181.13 (I6), U188.12 (A4), U193.13 (A2)
/myac_7: U23.9 (A7), U78.12 (A4), U98.3 (I1), U120.5, U130.5 (Q1), U144.3, U178.14 (I5), U178.15 (I4), U180.12 (I7), U180.13 (I6), U189.5 (A1), U193.15 (A3)
/myac_8: U22.2 (A0), U81.5 (A1), U97.3 (I1), U120.13, U130.7 (Q2), U144.11, U177.14 (I5), U177.15 (I4), U179.12 (I7), U179.13 (I6), U189.3 (A2), U194.10 (A0)
/myac_9: U22.3 (A1), U44.2, U81.3 (A2), U93.3 (I1), U130.10 (Q3), U144.12, U176.14 (I5), U176.15 (I4), U178.12 (I7), U178.13 (I6), U189.14 (A3), U194.12 (A1)
/myac_10: U22.4 (A2), U44.10, U81.14 (A3), U89.12, U104.3 (I1), U130.12 (Q4), U175.14 (I5), U175.15 (I4), U177.12 (I7), U177.13 (I6), U189.12 (A4), U194.13 (A2)
/myac_11: U22.5 (A3), U81.12 (A4), U89.13, U99.13 (I6), U103.3 (I1), U108.2, U110.12, U130.15 (Q5), U158.4, U175.13 (I6), U176.12 (I7), U176.13 (I6), U194.15 (A3)
/myacstep2_0: U148.8, U186.3 (I1)
/myacstep2_1: U160.12, U185.3 (I1)
/myacstep2_2: U160.6, U184.3 (I1)
/myacstep2_3: U160.8, U183.3 (I1)
/myacstep2_4: U150.12, U182.3 (I1)
/myacstep2_5: U82.6, U181.3 (I1)
/myacstep2_6: U82.8, U180.3 (I1)
/myacstep2_7: U82.11, U179.3 (I1)
/myacstep2_8: U107.3, U178.3 (I1)
/myacstep2_9: U107.6, U177.3 (I1)
/myacstep2_10: U107.8, U176.3 (I1)
/myacstep2_11: U107.11, U175.3 (I1)
/mylink: U22.8 (A6), U99.5 (Z)
/pause: U17.2 (A0), U127.12, U143.9, U167.12
/s3clk: U41.6 (~Q), U90.3 (C)
/sctr_0: U4.14 (Q0), U12.6 (A4), U151.5
/sctr_1: U4.13 (Q1), U16.9 (A7), U127.2
/sctr_2: U4.12 (Q2), U16.4 (A2), U113.13
/sctr_3: U4.11 (Q3), U11.7 (A5), U91.10
/sctr_4: U5.14 (Q0), U11.2 (A0), U109.5
/sctr_5: U5.13 (Q1), U147.2, U147.10, U150.10
/shllink: U41.9 (Q), U99.14 (I5), U99.15 (I4)
/tp1: U2.9, U13.18 (Y0), U143.3
/tp2: U3.11, U13.17 (Y1), U146.9, U161.4
/ts1: U17.13 (Y5), U54.12
/ts2: U17.12 (Y6), U141.1, U146.5
/ts3: U4.7 (CEP), U4.10 (CET), U5.7 (CEP), U17.11 (Y7), U90.4 (~S), U141.3, U158.5, U161.9, U161.13, U167.2, U168.12
/yreg_0: U12.17 (Y1), U75.6 (B1), U125.1, U192.9 (B0)
/yreg_1: U16.14 (Y4), U75.2 (B2), U125.3, U192.11 (B1)
/yreg_2: U11.11 (Y7), U75.15 (B3), U125.5, U192.14 (B2)
/yreg_3: U11.16 (Y2), U75.11 (B4), U125.9, U192.1 (B3)
/yreg_4: U15.13 (Y5), U78.6 (B1), U125.11, U193.9 (B0)
/yreg_5: U15.17 (Y1), U78.2 (B2), U125.13, U193.11 (B1)
/yreg_6: U10.13 (Y5), U78.15 (B3), U124.1, U193.14 (B2)
/yreg_7: U10.17 (Y1), U78.11 (B4), U124.3, U193.1 (B3)
/yreg_8: U14.13 (Y5), U81.6 (B1), U124.5, U194.9 (B0)
/yreg_9: U14.17 (Y1), U81.2 (B2), U124.9, U194.11 (B1)
/yreg_10: U9.13 (Y5), U81.15 (B3), U124.11, U194.14 (B2)
/yreg_11: U9.17 (Y1), U81.11 (B4), U124.13, U194.1 (B3)
GND: J1.36, J2.36, J3.36, J4.36, U1.7 (GND), U2.7 (GND), U3.7 (GND), U4.8 (GND), U5.5 (D2), U5.6 (D3), U5.8 (GND), U6.7 (GND), U8.7 (GND), U9.1 (G1), U9.10 (GND), U9.19 (G2), U10.1 (G1), U10.10 (GND), U10.19 (G2), U11.1 (G1), U11.10 (GND), U11.19 (G2), U12.1 (G1), U12.10 (GND), U12.19 (G2), U13.1 (G1), U13.4 (A2), U13.5 (A3), U13.6 (A4), U13.7 (A5), U13.8 (A6), U13.9 (A7), U13.10 (GND), U13.19 (G2), U14.1 (G1), U14.10 (GND), U14.19 (G2), U15.1 (G1), U15.10 (GND), U15.19 (G2), U16.1 (G1), U16.10 (GND), U16.19 (G2), U17.1 (G1), U17.10 (GND), U17.19 (G2), U22.9 (A7), U22.10 (GND), U23.10 (GND), U24.8 (GND), U25.8 (GND), U25.10 (I1c), U25.11 (I0c), U25.13 (I1d), U25.14 (I0d), U30.2 (I0a), U30.5 (I0b), U30.8 (GND), U30.14 (I0d), U41.7 (GND), U44.7 (GND), U51.7 (GND), U54.7 (GND), U75.7 (C0), U75.8 (GND), U78.8 (GND), U81.8 (GND), U82.7 (GND), U89.7 (GND), U90.7 (GND), U91.7 (GND), U92.4 (I0), U92.7 (~E), U92.8 (GND), U93.4 (I0), U93.7 (~E), U93.8 (GND), U94.4 (I0), U94.7 (~E), U94.8 (GND), U95.4 (I0), U95.7 (~E), U95.8 (GND), U96.4 (I0), U96.7 (~E), U96.8 (GND), U96.14 (I5), U96.15 (I4), U97.4 (I0), U97.7 (~E), U97.8 (GND), U98.4 (I0), U98.7 (~E), U98.8 (GND), U99.2 (I2), U99.7 (~E), U99.8 (GND), U99.12 (I7), U100.4 (I0), U100.7 (~E), U100.8 (GND), U101.4 (I0), U101.7 (~E), U101.8 (GND), U102.4 (I0), U102.7 (~E), U102.8 (GND), U103.4 (I0), U103.7 (~E), U103.8 (GND), U104.4 (I0), U104.7 (~E), U104.8 (GND), U107.7 (GND), U108.7 (GND), U109.7 (GND), U110.7 (GND), U113.7 (GND), U120.7 (GND), U122.7 (GND), U124.7 (GND), U125.7 (GND), U127.7 (GND), U129.8 (GND), U130.8 (GND), U131.8 (GND), U132.8 (GND), U139.8 (GND), U139.13 (D3), U141.7 (GND), U142.7 (GND), U143.7 (GND), U144.7 (GND), U145.7 (GND), U146.7 (GND), U147.7 (GND), U148.7 (GND), U149.7 (GND), U150.7 (GND), U151.7 (GND), U152.7 (GND), U154.7 (GND), U157.7 (GND), U158.7 (GND), U160.7 (GND), U161.7 (GND), U162.7 (GND), U167.7 (GND), U168.7 (GND), U175.8 (GND), U175.12 (I7), U176.8 (GND), U177.8 (GND), U178.8 (GND), U179.8 (GND), U180.8 (GND), U181.8 (GND), U182.8 (GND), U183.8 (GND), U184.8 (GND), U185.8 (GND), U186.8 (GND), U187.8 (GND), U188.8 (GND), U189.8 (GND), U192.2 (Ia<b), U192.4 (Ia>b), U192.8 (GND), U193.8 (GND), U194.8 (GND)
unnamed: U4.15 (TC), U5.10 (CET)
unnamed: U25.15 (E), U30.15 (E), U167.8
unnamed: U25.1 (S), U30.1 (S), U158.8
unnamed: U5.3 (D0), U25.4 (Za)
unnamed: U5.4 (D1), U25.7 (Zb)
unnamed: U4.3 (D0), U30.4 (Za)
unnamed: U4.4 (D1), U30.7 (Zb)
unnamed: U4.5 (D2), U30.9 (Zc)
unnamed: U4.6 (D3), U30.12 (Zd)
unnamed: U41.2 (D), U143.8
unnamed: U41.12 (D), U147.11
unnamed: U75.9 (C4), U78.7 (C0)
unnamed: U78.9 (C4), U81.7 (C0)
unnamed: U90.12 (D), U127.11
unnamed: U90.8 (~Q), U143.11
unnamed: U107.1, U120.11
unnamed: U107.2, U113.3
unnamed: U44.3, U107.4
unnamed: U44.6, U107.5
unnamed: U44.8, U107.9
unnamed: U44.11, U107.10
unnamed: U107.12, U108.3
unnamed: U107.13, U108.6
unnamed: U82.5, U108.8
unnamed: U82.9, U108.11
unnamed: U109.3, U150.1
unnamed: U109.6, U150.2
unnamed: U109.8, U150.13
unnamed: U82.4, U109.11
unnamed: U113.6, U160.13
unnamed: U113.8, U160.3
unnamed: U113.11, U160.4
unnamed: U82.10, U120.3
unnamed: U82.12, U120.6
unnamed: U82.13, U120.8
unnamed: U122.8, U167.13
unnamed: U122.9, U147.3
unnamed: U122.10, U150.8
unnamed: U122.12, U147.6
unnamed: U122.13, U147.8
unnamed: U127.3, U160.2
unnamed: U51.6, U127.8
unnamed: U2.8, U24.9 (Cp), U139.9 (Cp)
unnamed: U51.4, U139.12 (D2)
unnamed: U54.5, U141.12
unnamed: U89.11, U141.13
unnamed: U143.6, U149.1
unnamed: U144.1, U162.11
unnamed: U144.4, U144.8
unnamed: U144.13, U162.12
unnamed: U51.10, U145.2, U145.4
unnamed: U51.2, U51.11, U145.8
unnamed: U146.8, U158.12
unnamed: U146.3, U146.12
unnamed: U147.12, U158.3
unnamed: U147.13, U158.6
unnamed: U148.9, U151.3
unnamed: U148.10, U151.6
unnamed: U148.11, U151.8
unnamed: U149.2, U161.6
unnamed: U149.3, U149.9, U161.11
unnamed: U149.4, U149.10, U161.8
unnamed: U51.5, U150.6
unnamed: U151.11, U160.1
unnamed: U152.6, U162.5
unnamed: U152.8, U162.6
unnamed: U152.12, U162.4
unnamed: U154.6, U162.2
unnamed: U154.8, U162.3
unnamed: U154.12, U162.1
unnamed: U82.3, U157.4
unnamed: U91.3, U160.5
unnamed: U91.6, U160.9
unnamed: U91.8, U160.10
unnamed: U91.11, U160.11
unnamed: U54.4, U162.8
unnamed: U3.10, U168.9
unnamed: U187.9 (C4), U188.7 (C0)
unnamed: U188.9 (C4), U189.7 (C0)
unnamed: U192.7 (Oa<b), U193.2 (Ia<b)
unnamed: U192.6 (Oa=b), U193.3 (Ia=b)
unnamed: U192.5 (Oa>b), U193.4 (Ia>b)
unnamed: U193.7 (Oa<b), U194.2 (Ia<b)
unnamed: U193.6 (Oa=b), U194.3 (Ia=b)
unnamed: U193.5 (Oa>b), U194.4 (Ia>b)
unnamed: U90.2 (D), U194.7 (Oa<b)
VCC: J1.1, J2.1, J3.1, J4.1, U1.14 (VCC), U2.14 (VCC), U3.14 (VCC), U4.16 (VCC), U5.16 (VCC), U6.14 (VCC), U8.14 (VCC), U9.20 (VCC), U10.20 (VCC), U11.20 (VCC), U12.20 (VCC), U13.20 (VCC), U14.20 (VCC), U15.20 (VCC), U16.20 (VCC), U17.20 (VCC), U22.6 (A4), U22.7 (A5), U22.20 (VCC), U23.20 (VCC), U24.16 (VCC), U25.2 (I0a), U25.5 (I0b), U25.6 (I1b), U25.16 (VCC), U30.11 (I0c), U30.16 (VCC), U41.1 (~R), U41.4 (~S), U41.10 (~S), U41.13 (~R), U41.14 (VCC), U44.14 (VCC), U51.14 (VCC), U54.14 (VCC), U75.16 (VCC), U78.16 (VCC), U81.16 (VCC), U82.14 (VCC), U89.14 (VCC), U90.1 (~R), U90.10 (~S), U90.14 (VCC), U91.14 (VCC), U92.16 (VCC), U93.16 (VCC), U94.16 (VCC), U95.16 (VCC), U96.16 (VCC), U97.16 (VCC), U98.16 (VCC), U99.16 (VCC), U100.16 (VCC), U101.16 (VCC), U102.16 (VCC), U103.16 (VCC), U104.16 (VCC), U107.14 (VCC), U108.14 (VCC), U109.14 (VCC), U110.14 (VCC), U113.14 (VCC), U120.14 (VCC), U122.14 (VCC), U124.14 (VCC), U125.14 (VCC), U127.14 (VCC), U129.1 (~Mr), U129.16 (VCC), U130.1 (~Mr), U130.16 (VCC), U131.16 (VCC), U132.16 (VCC), U139.16 (VCC), U141.14 (VCC), U142.14 (VCC), U143.14 (VCC), U144.14 (VCC), U145.14 (VCC), U146.14 (VCC), U147.14 (VCC), U148.14 (VCC), U149.14 (VCC), U150.14 (VCC), U151.14 (VCC), U152.14 (VCC), U154.14 (VCC), U157.1, U157.2, U157.3, U157.14 (VCC), U158.14 (VCC), U160.14 (VCC), U161.14 (VCC), U162.14 (VCC), U167.14 (VCC), U168.14 (VCC), U175.16 (VCC), U176.16 (VCC), U177.16 (VCC), U178.16 (VCC), U179.16 (VCC), U180.16 (VCC), U181.16 (VCC), U182.16 (VCC), U183.16 (VCC), U184.16 (VCC), U185.16 (VCC), U186.16 (VCC), U187.7 (C0), U187.16 (VCC), U188.16 (VCC), U189.16 (VCC), U192.3 (Ia=b), U192.16 (VCC), U193.16 (VCC), U194.16 (VCC)

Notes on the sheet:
multiply step is a shift right when multiplier bit is zero
doing execute cycle of extended arithmetic * in FETCH cycle if no memory operand * in EXEC cycle if has memory operand
pause processor at beginning of TS3 while doing step 3 resume when termination condition met
perform step 3 clocking while processor pausing at beginning of TS3 make sure all pulses have full width
clock SCTR at TP2 or while step 3 stepping
divide step is a shift left when quotient bit is zero
LINK bit for left shifts: * loaded at TP2 from processor LINK * clocked by s3clk pulses during shifts
memory operand follows opcode retained in MBUF by processor throughout EXEC cycle
SHL,ASR,LSR
acsel condition 0 TS1 & msfetch - get initial ACUM contents into MYAC 1 TS2 & extarex - get step 2 results into ACUM 2 TS3 & (extop31 == 2 & muymbit) - MUY step with multiplier bit set 3 TS3 & (extop31 == 3 & dviqbit) - DVI step with quotient bit set 4 TS3 & (extop31 == 4) - NMI step 5 TS3 & (extop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
load 0 at TP2 for NMI load 20 at TP2 for MUY,DVI load ~YREG at TP2 for SCL,SHL,ASR,LSR
enable incrementing during TS3 (step 3)
opcode clocked at TP1 during FETCH * extar = it is an extended arith opcode * memop = the opcode has memory operand
TP2 & extarex: load step2 result
s3clk: shift/arith step
shift registers clock on posedge s3clk - 300nS for MUY,DVI - 200nS for NMI,SHL,ASR,LSR
has memory operand SCL,MUY,DVI,SHL,ASR,LSR
dviover = (myac >= yreg)
TP1 & FETCH: load ACUM or zero
extop<3:1> 0 : NOP : new link = old link 1 : SCL : new link = old link 2 : MUY : new link = 0 3 : DVI : new link = overflow 4 : NMI : new link = last bit shifted out 5 : SHL : new link = last bit shifted out 6 : ASR : new link = sign bit 7 : LSR : new link = 0
clear SCTR on bus init
enable loading during TS2 for extarex cycles and extop<3:1> ne 000

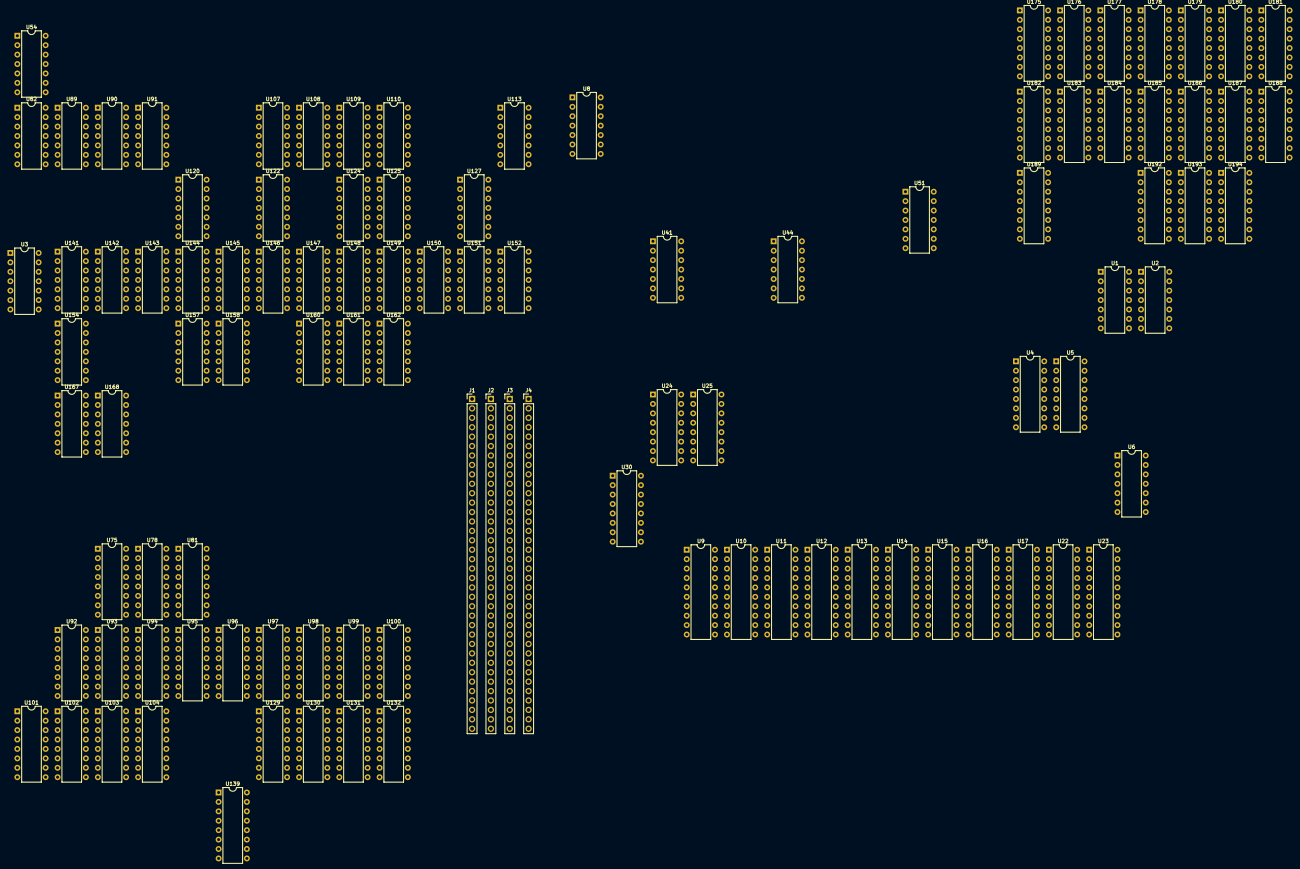
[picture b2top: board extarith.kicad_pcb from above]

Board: 2 copper layers, 102 parts (0 on the bottom side), 359 nets, no tracks yet.
